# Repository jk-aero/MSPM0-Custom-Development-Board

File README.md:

# MSPM0-Custom-Development-Board

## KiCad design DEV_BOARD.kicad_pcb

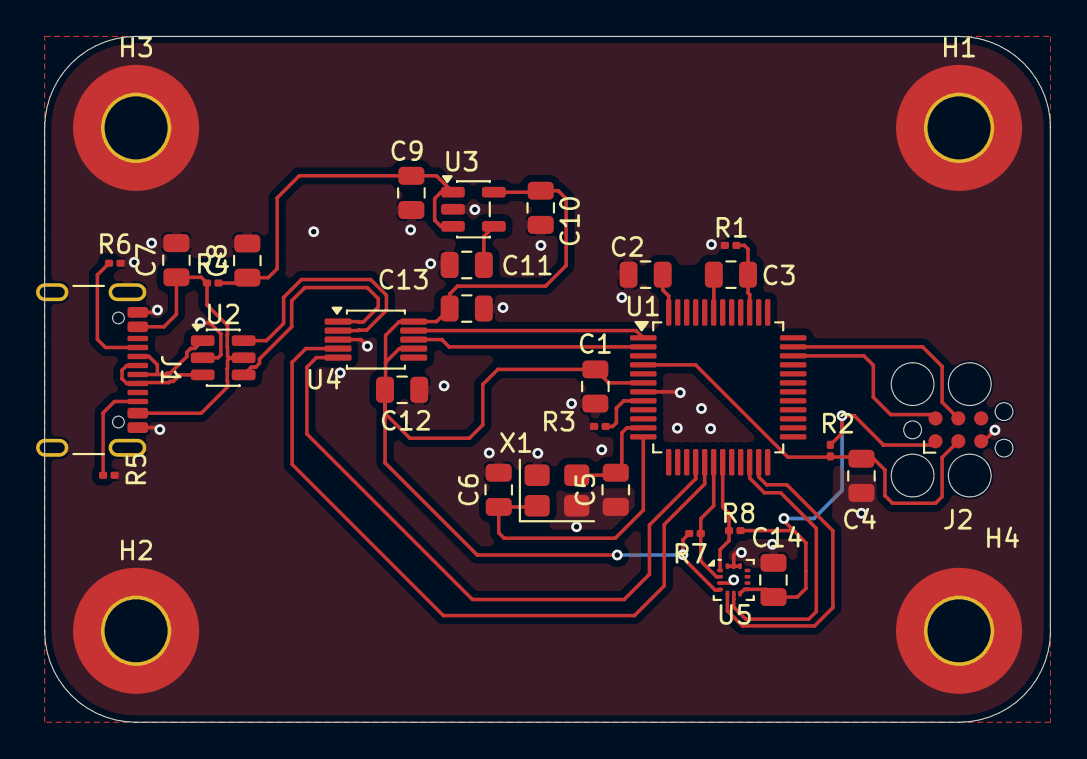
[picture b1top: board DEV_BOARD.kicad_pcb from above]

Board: 2 copper layers, 55.9 x 38.1 mm, 34 parts (0 on the bottom side), 28 nets.

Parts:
C1, C7, C8, C9, C10, C11: 10u; C_0805_2012Metric
C2, C3, C4, C12, C13, C14: 470n; C_0805_2012Metric
C5, C6: 15p; C_0805_2012Metric
H1, H2, H3, H4: M3; MountingHole_3.5mm_Pad_TopOnly
J1: USB_C_Receptacle_USB2.0_16P; USB_C_Receptacle_GCT_USB4105-xx-A_16P_TopMnt_Horizontal
J2: Conn_ARM_SWD_TagConnect_TC2030; Tag-Connect_TC2030-IDC-FP_2x03_P1.27mm_Vertical
R1, R4: 0R; R_0201_0603Metric
R2, R5, R6, R7, R8: 5k1; R_0201_0603Metric
R3: 100K; R_0201_0603Metric
U1: MSPM0G350x; LQFP-48_7x7mm_P0.5mm
U2: USBLC6-2SC6; SOT-23-6
U3: SPX3819M5-L-3-3; SOT-23-5
U4: CH340E; MSOP-10_3x3mm_P0.5mm
U5: LIS2DH; LGA-14_2x2mm_P0.35mm_LayoutBorder3x4y
X1: 8MHz; Crystal_SMD_3225-4Pin_3.2x2.5mm

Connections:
+1V35: C2.1, U1.48 (VCORE)
+3V3: C1.1, C10.1, C12.1, C13.1, C14.1, J2.1 (VCC), R2.1, R7.1, R8.1, U1.6 (VDD), U3.5 (OUT), U4.7 (VCC), U4.10 (V3), U5.4 (~CS), U5.7 (Vdd_IO), U5.8 (Vdd)
+VBUS: C7.1, J1.A4 (VBUS), J1.A9 (VBUS), J1.B4 (VBUS), J1.B9 (VBUS), R4.1, U2.5 (VBUS)
+VBUSF: C8.1, C9.1, R4.2, U3.1 (IN), U3.3 (EN)
/CC1: J1.A5 (CC1), R6.1
/CC2: J1.B5 (CC2), R5.1
/HFXIN: C5.2, U1.11 (PA5/HFXIN/FCC_IN), X1.3
/HFXOUT: C6.2, U1.12 (PA6/HFCLK_IN/HFXOUT), X1.1
/NRST: C4.1, J2.3 (~RESET), R2.2, U1.4 (NRST)
/RSOC: R3.2, U1.8 (PA2/ROSC)
/UART0CTS: U1.17 (PA9/RTC_OUT/CLK_OUT), U4.4 (~RTS)
/UART0RTS: U1.16 (PA8), U4.5 (~CTS)
/UART0RX: U1.2 (PA1), U4.8 (TXD)
/UART0TX: U1.1 (PA0/FCC_IN), U4.9 (RXD)
/USBCD+: J1.A6 (D+), J1.B6 (D+), U2.3 (I/O2)
/USBCD-: J1.A7 (D-), J1.B7 (D-), U2.1 (I/O1)
/USBD+: U2.4 (I/O2), U4.1 (UD+)
/USBD-: U2.6 (I/O1), U4.2 (UD-)
/VREF+: C3.1, U1.43 (PA23/VREF+)
/VREF-: C3.2, R1.1, U1.39 (PA21/A1_7/VREF)
GND: C1.2, C2.2, C4.2, C5.1, C6.1, C7.2, C8.2, C9.2, C10.2, C11.2, C12.2, C13.2, C14.2, H1.1 (1_1), H2.1 (1_1), H3.1 (1_1), H4.1 (1_1), J1.A1 (GND), J1.A12 (GND), J1.B1 (GND), J1.B12 (GND), J1.SH (SHIELD), J2.5 (GND), R1.2, R3.1, R5.2, R6.2, U1.7 (VSS), U2.2 (GND), U3.2 (GND), U4.3 (GND), U5.3 (SDO), U5.9 (GND), U5.10 (GND), U5.11 (GND), U5.12 (GND), U5.13 (GND), U5.14 (GND), X1.2 (G), X1.4 (G)
INT1: U1.22 (PB8), U5.6 (INT1)
INT2: U1.23 (PB9), U5.5 (INT2)
unnamed: J2.4 (SWCLK), U1.35 (PA20/SWCLK)
unnamed: J2.2 (SWDIO), U1.34 (PA19/SWDIO)
unnamed: C11.1, U3.4 (BP)
SCL: R8.2, U1.19 (PA11), U5.1 (SCL/SPC)
SDA: R7.2, U1.18 (PA10/CLK_OUT), U5.2 (SDA/SDI)

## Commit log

2026-06-20 Part 1: Creating the MCU
2026-06-20 Part 2: Building the Core MCU Circuit
2026-06-26 Routing completed
